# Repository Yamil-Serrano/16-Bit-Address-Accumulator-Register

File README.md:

# 16-Bit-Address-Accumulator-Register

A 16-Bit address accumulator register designed with discrete 74LS and 74HC series TTL logic. This register allows my custom 4-Bit CPU to use a register's data to increment or decrement the Address Register. That way, we can address up to 64KB of RAM, using only 4-bit steps inside a 16-bit address space.

## Overview

If we use a register's data or the ALU's output from a 4-bit CPU, we can only access 16 bytes of RAM, which is not enough for decent algorithms or small video games. To solve this, this Memory Address Register uses an internal adder that takes 4 bits coming from a register in the register file (or from the ALU) and adds or subtracts it (depending on the selected operation) from the 16-bit address stored inside the register. This way, we can use a 16-bit address bus, which gives us up to approximately 64 KB of RAM. This allows us to store more data for our programs and build more complex applications.

## Architecture

This small module uses two's complement to perform subtraction. The DEC pin controls both the carry-in of the first 74HC283 full adder and the XOR gates that negate the incoming data. When DEC is 1, the first adder receives a carry-in of 1, and the XOR gates invert the input data. This performs a two's complement operation, allowing us to move backward and forward within the 16-bit address space.

The 16-bit register is built using four 74HC173 ICs. Its outputs serve as both the memory address and the A operand of the full adders. The full adders receive the register's output as operand A, and the incoming 4-bit data (expanded to 16 bits) as operand B.

## Schematic

## Components Used
| IC | Function | Quantity | Purpose |
|---|---|---|---|
| 74HC283 | 4-bit Full Adder | 4 | Performs the 16-bit addition/subtraction |
| 74HC173 | 4-bit Register | 4 | Stores the 16-bit address |
| 74HC86 | Quad 2-input XOR | 4 | Inverts the input data for two's complement subtraction |

## Control Pins
This module has four control pins:

- **NS (Not Store)**: Controls the store function of the 74HC173 registers. When 0, the internal registers store the new address coming from the adders. When 1, the registers do not store the new address, allowing us to freeze the address while other instructions are executed.

- **MR (Master Reset)**: Resets the internal registers. When 1, the registers reset to 0x0, giving us the address value 0x0000.
- **DEC (Decrement)**: Selects whether to add or subtract the incoming data from our address register.
- **CP (Clock Pulse)**: The clock signal for the internal registers.

## Verification

The module was verified on a breadboard using an Arduino Mega 2560 as a test controller. A dedicated test [`firmware`](./src/tester/src) was written to exercise the accumulator's read and write logic, validating both increment and decrement operations across the entire address space.

The test sequence performs the following steps:
1. Resets the internal register to `0x0000`.
2. Increments the MAR by `15` (0x0F) repeatedly until it reaches `0xFFFF`.
3. Decrements the MAR by `15` (0x0F) repeatedly until it returns to `0x0000`.

Each step is compared against the expected result, and the test suite prints a formatted table with `OK` or `FAIL` for every operation.

**Test Output Sample:**
```text
| MAR: 0x0000 | Data: 0x000F | Op: Inc | Expected: 0x000F | Got: 0x000F | OK |
| MAR: 0x000F | Data: 0x000F | Op: Inc | Expected: 0x001E | Got: 0x001E | OK |
...
| MAR: 0x0010 | Data: 0x000F | Op: Dec | Expected: 0x0001 | Got: 0x0001 | OK |
| MAR: 0x0001 | Data: 0x000F | Op: Dec | Expected: 0x0000 | Got: 0x0000 | OK |
```

## License

Licensed under the Solderpad Hardware License v2.1.
See the LICENSE file for full terms.

## Contact

If you have any questions or suggestions, feel free to reach out:

- GitHub: [Neowizen](https://github.com/Neowizen)

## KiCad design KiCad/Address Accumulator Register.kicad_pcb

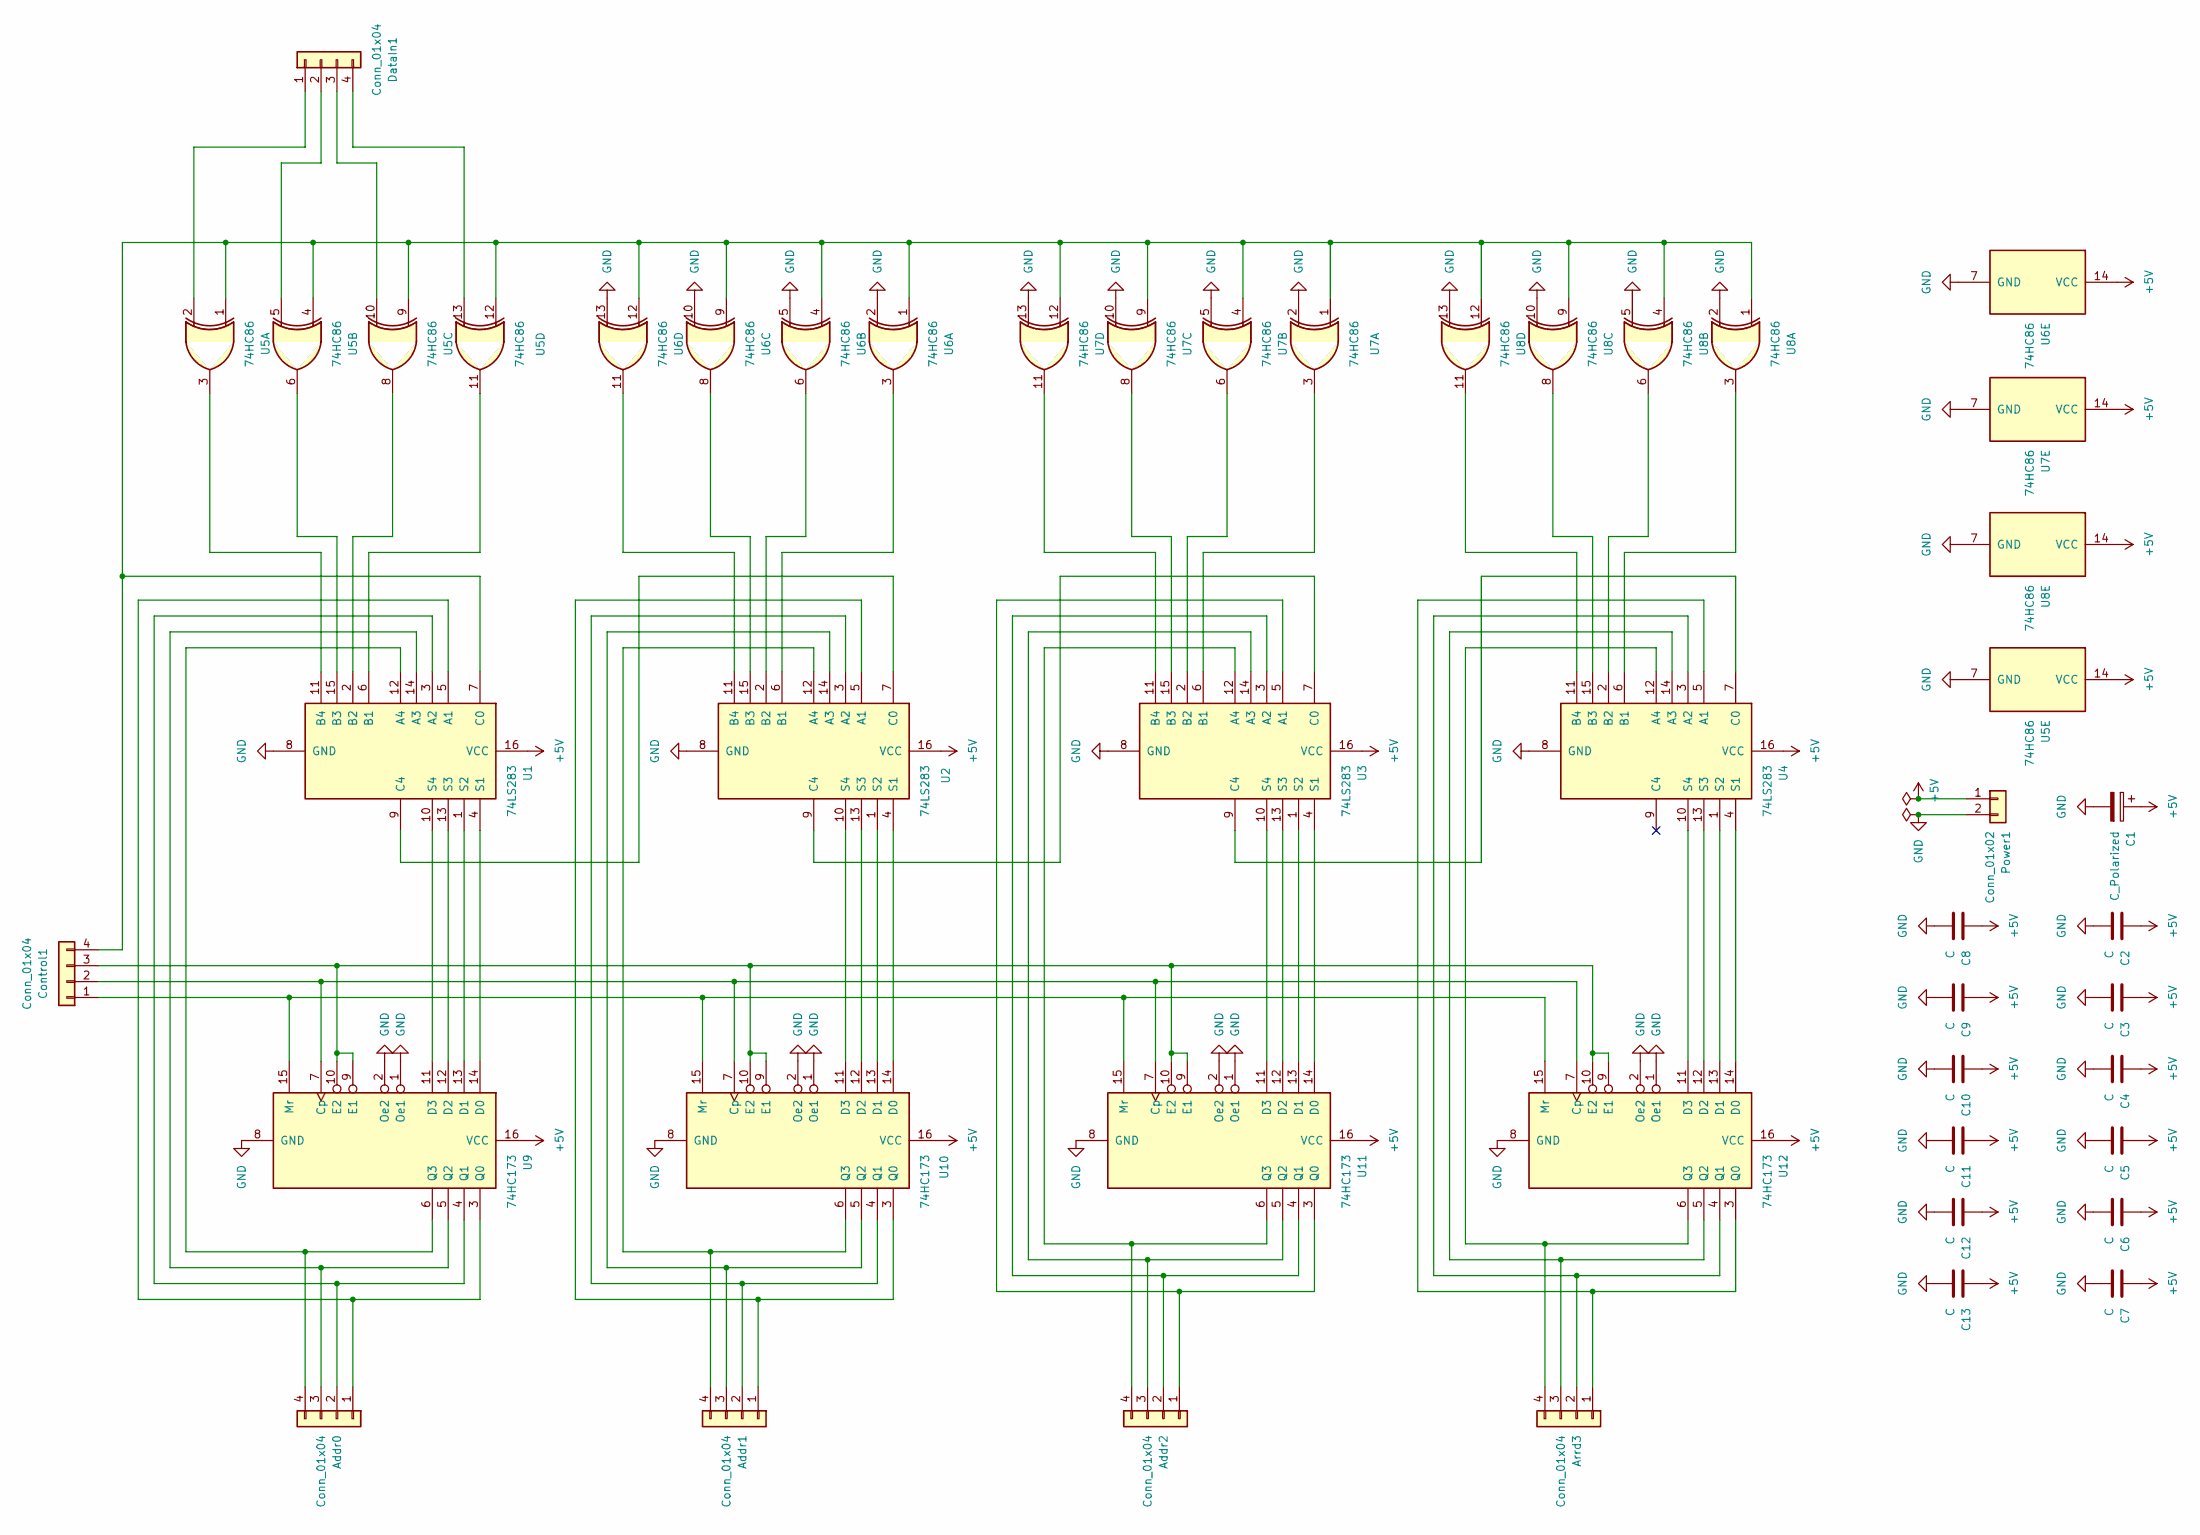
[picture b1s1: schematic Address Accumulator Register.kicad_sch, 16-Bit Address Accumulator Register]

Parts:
Addr0, Addr1, Addr2: Conn_01x04; PinHeader_1x04_P2.54mm_Vertical
Arrd3: Conn_01x04; PinHeader_1x04_P2.54mm_Vertical
C1: C_Polarized; CP_Radial_D4.0mm_P1.50mm
C2, C3, C4, C5, C6, C7, C8, C9, C10, C11, C12, C13: C; C_Disc_D3.0mm_W1.6mm_P2.50mm
Control1: Conn_01x04; PinHeader_1x04_P2.54mm_Vertical
DataIn1: Conn_01x04; PinHeader_1x04_P2.54mm_Vertical
Power1: Conn_01x02; PinHeader_1x02_P2.54mm_Vertical
U1, U2, U3, U4: 74LS283; DIP-16_W7.62mm_Socket
U5, U6, U7, U8: 74HC86; DIP-14_W7.62mm_Socket
U9, U10, U11, U12: 74HC173; DIP-16_W7.62mm_Socket

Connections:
+5V: C1.1, C2.1, C3.1, C4.1, C5.1, C6.1, C7.1, C8.1, C9.1, C10.1, C11.1, C12.1, C13.1, Power1.1, U1.16 (VCC), U2.16 (VCC), U3.16 (VCC), U4.16 (VCC), U5.14 (VCC), U6.14 (VCC), U7.14 (VCC), U8.14 (VCC), U9.16 (VCC), U10.16 (VCC), U11.16 (VCC), U12.16 (VCC)
GND: C1.2, C2.2, C3.2, C4.2, C5.2, C6.2, C7.2, C8.2, C9.2, C10.2, C11.2, C12.2, C13.2, Power1.2, U1.8 (GND), U2.8 (GND), U3.8 (GND), U4.8 (GND), U5.7 (GND), U6.2, U6.5, U6.7 (GND), U6.10, U6.13, U7.2, U7.5, U7.7 (GND), U7.10, U7.13, U8.2, U8.5, U8.7 (GND), U8.10, U8.13, U9.1 (Oe1), U9.2 (Oe2), U9.8 (GND), U10.1 (Oe1), U10.2 (Oe2), U10.8 (GND), U11.1 (Oe1), U11.2 (Oe2), U11.8 (GND), U12.1 (Oe1), U12.2 (Oe2), U12.8 (GND)
unnamed: Addr0.1, U1.5 (A1), U9.3 (Q0)
unnamed: Addr0.2, U1.3 (A2), U9.4 (Q1)
unnamed: Addr0.3, U1.14 (A3), U9.5 (Q2)
unnamed: Addr0.4, U1.12 (A4), U9.6 (Q3)
unnamed: Addr1.1, U2.5 (A1), U10.3 (Q0)
unnamed: Addr1.2, U2.3 (A2), U10.4 (Q1)
unnamed: Addr1.3, U2.14 (A3), U10.5 (Q2)
unnamed: Addr1.4, U2.12 (A4), U10.6 (Q3)
unnamed: Addr2.1, U3.5 (A1), U11.3 (Q0)
unnamed: Addr2.2, U3.3 (A2), U11.4 (Q1)
unnamed: Addr2.3, U3.14 (A3), U11.5 (Q2)
unnamed: Addr2.4, U3.12 (A4), U11.6 (Q3)
unnamed: Arrd3.1, U4.5 (A1), U12.3 (Q0)
unnamed: Arrd3.2, U4.3 (A2), U12.4 (Q1)
unnamed: Arrd3.3, U4.14 (A3), U12.5 (Q2)
unnamed: Arrd3.4, U4.12 (A4), U12.6 (Q3)
unnamed: Control1.1, U9.15 (Mr), U10.15 (Mr), U11.15 (Mr), U12.15 (Mr)
unnamed: Control1.2, U9.7 (Cp), U10.7 (Cp), U11.7 (Cp), U12.7 (Cp)
unnamed: Control1.3, U9.9 (E1), U9.10 (E2), U10.9 (E1), U10.10 (E2), U11.9 (E1), U11.10 (E2), U12.9 (E1), U12.10 (E2)
unnamed: Control1.4, U1.7 (C0), U5.1, U5.4, U5.9, U5.12, U6.1, U6.4, U6.9, U6.12, U7.1, U7.4, U7.9, U7.12, U8.1, U8.4, U8.9, U8.12
unnamed: DataIn1.1, U5.2
unnamed: DataIn1.2, U5.5
unnamed: DataIn1.3, U5.10
unnamed: DataIn1.4, U5.13
unnamed: U1.6 (B1), U5.11
unnamed: U1.2 (B2), U5.8
unnamed: U1.15 (B3), U5.6
unnamed: U1.11 (B4), U5.3
unnamed: U1.9 (C4), U2.7 (C0)
unnamed: U1.4 (S1), U9.14 (D0)
unnamed: U1.1 (S2), U9.13 (D1)
unnamed: U1.13 (S3), U9.12 (D2)
unnamed: U1.10 (S4), U9.11 (D3)
unnamed: U2.6 (B1), U6.3
unnamed: U2.2 (B2), U6.6
unnamed: U2.15 (B3), U6.8
unnamed: U2.11 (B4), U6.11
unnamed: U2.9 (C4), U3.7 (C0)
unnamed: U3.6 (B1), U7.3
unnamed: U3.2 (B2), U7.6
unnamed: U3.15 (B3), U7.8
unnamed: U3.11 (B4), U7.11
unnamed: U3.9 (C4), U4.7 (C0)
unnamed: U4.6 (B1), U8.3
unnamed: U4.2 (B2), U8.6
unnamed: U4.15 (B3), U8.8
unnamed: U4.11 (B4), U8.11
unnamed: U2.4 (S1), U10.14 (D0)
unnamed: U2.1 (S2), U10.13 (D1)
unnamed: U2.13 (S3), U10.12 (D2)
unnamed: U2.10 (S4), U10.11 (D3)
unnamed: U3.4 (S1), U11.14 (D0)
unnamed: U3.1 (S2), U11.13 (D1)
unnamed: U3.13 (S3), U11.12 (D2)
unnamed: U3.10 (S4), U11.11 (D3)
unnamed: U4.4 (S1), U12.14 (D0)
unnamed: U4.1 (S2), U12.13 (D1)
unnamed: U4.13 (S3), U12.12 (D2)
unnamed: U4.10 (S4), U12.11 (D3)

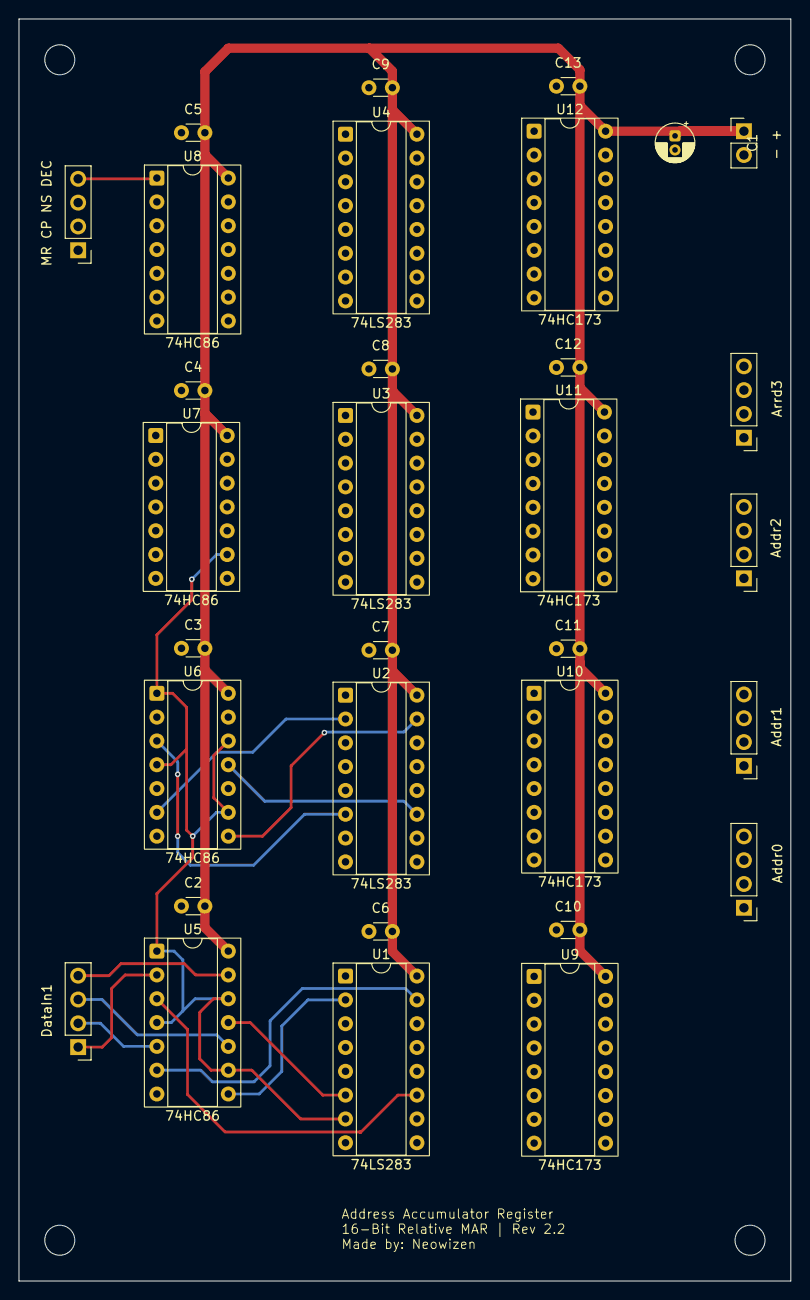
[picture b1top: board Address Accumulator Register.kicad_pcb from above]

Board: 2 copper layers, 82.3 x 134.6 mm, 32 parts (0 on the bottom side), 61 nets.
